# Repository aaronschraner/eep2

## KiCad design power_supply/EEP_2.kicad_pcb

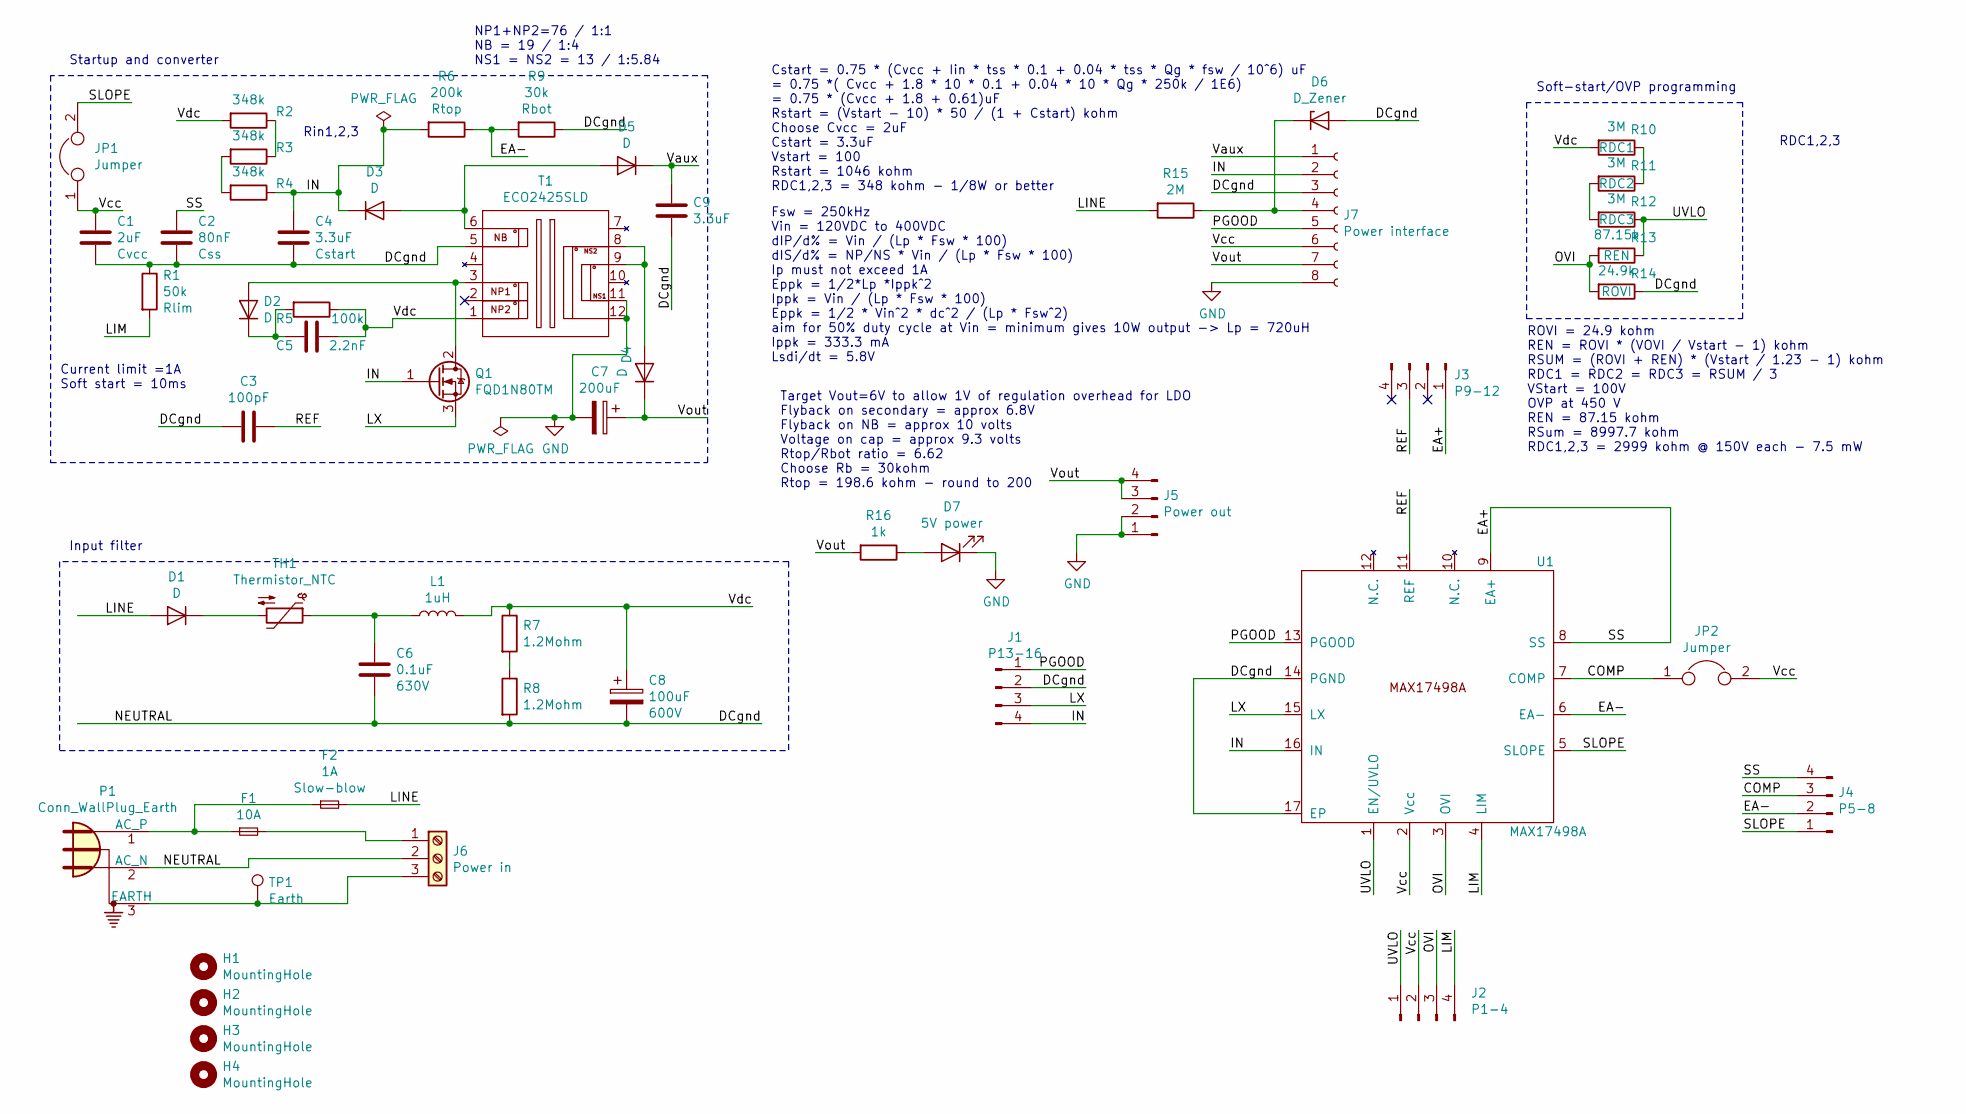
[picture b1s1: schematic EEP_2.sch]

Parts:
C1: 2uF; C_0805_2012Metric
C2: 80nF; C_0805_2012Metric
C3: 100pF; C_0805_2012Metric
C4: 3.3uF; C_1210_3225Metric
C5: 2.2nF; C_0805_2012Metric
C6: 0.1uF; C_2220_5650Metric; Voltage rating 630V
C7: 200uF; CP_Elec_6.3x7.7
C8: 100uF; CP_Radial_D30.0mm_P10.00mm_SnapIn; Voltage rating 600V
C9: 3.3uF; C_0805_2012Metric
D1, D4: D; D_SMC
D2, D3, D5: D; D_SMA
D6: D_Zener; D_SMA
D7: 5V power; LED_0805_2012Metric
F1: 10A; Fuseholder_Cylinder-5x20mm_Schurter_0031_8201_Horizontal_Op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
F2: 1A; Fuseholder_Cylinder-5x20mm_Schurter_0031_8201_Horizontal_Op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
H1, H2, H3, H4: MountingHole; MountingHole_3.2mm_M3_ISO7380
J1: P13-16; PinHeader_1x04_P2.54mm_Vertical
J2: P1-4; PinHeader_1x04_P2.54mm_Vertical
J3: P9-12; PinHeader_1x04_P2.54mm_Vertical
J4: P5-8; PinHeader_1x04_P2.54mm_Vertical
J5: Power out; PinHeader_1x04_P2.54mm_Vertical
J6: Power in; PhoenixContact_GMSTB_2,5_3-GF-7,62_1x03_P7.62mm_Horizontal_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
J7: Power interface; PinSocket_1x08_P2.54mm_Vertical
JP1, JP2: Jumper; SolderJumper-2_P1.3mm_Open_RoundedPad1.0x1.5mm
L1: 1uH; L_1008_2520Metric
P1: Conn_WallPlug_Earth; PhoenixContact_GMSTB_2,5_3-GF-7,62_1x03_P7.62mm_Horizontal_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
Q1: FQD1N80TM; TO-252-2
R1: 50k; R_0805_2012Metric
R2, R3, R4: 348k; R_0805_2012Metric
R5: 100k; R_2512_6332Metric
R6: 200k; R_0805_2012Metric
R7, R8: 1.2Mohm; R_0805_2012Metric
R9: 30k; R_0805_2012Metric
R10, R11, R12: 3M; R_0805_2012Metric
R13: 87.15k; R_0805_2012Metric
R14: 24.9k; R_0805_2012Metric
R15: 2M; R_0805_2012Metric
R16: 1k; R_0805_2012Metric
T1: ECO2425SLD; ECO2425SLD-D01H017
TH1: Thermistor_NTC; R_Axial_DIN0204_L3.6mm_D1.6mm_P5.08mm_Horizontal
TP1: Earth; TestPoint_Loop_D2.50mm_Drill1.0mm
U1: MAX17498A; TQFN-16-1EP_3x3mm_P0.5mm_EP1.23x1.23mm

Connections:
/COMP: J4.3, JP2.1, U1.7 (COMP)
/DCgnd: C1.2, C2.2, C3.2, C4.1, C6.2, C8.2, C9.2, D6.2 (A), J1.2, J6.2, J7.3, P1.2 (AC_N), R1.1, R8.2, R9.1, R14.1, T1.5, U1.14 (PGND), U1.17 (EP)
/EA+: C2.1, J3.1, J4.4, U1.8 (SS), U1.9 (EA+)
/EA-: J4.2, R6.1, R9.2, U1.6 (EA-)
/IN: C4.2, D3.1 (K), J1.4, J7.2, Q1.1 (G), R4.1, R6.2, U1.16 (IN)
/LIM: J2.4, R1.2, U1.4 (LIM)
/LINE: D1.2 (A), F2.2, R15.2
/LX: J1.3, Q1.3 (S), U1.15 (LX)
/OVI: J2.3, R13.2, R14.2, U1.3 (OVI)
/PGOOD: J1.1, J7.5, U1.13 (PGOOD)
/REF: C3.1, J3.3, U1.11 (REF)
/SLOPE: J4.1, JP1.2, U1.5 (SLOPE)
/UVLO: J2.1, R12.1, R13.1, U1.1 (EN/UVLO)
/Vaux: C9.1, D5.1 (K), J7.1
/Vcc: C1.1, J2.2, J7.6, JP1.1, JP2.2, U1.2 (Vcc)
/Vdc: C5.2, C8.1, L1.2, R2.2, R5.1, R7.1, R10.2, T1.1
/Vout: C7.1, D4.1 (K), J5.3, J5.4, J7.7, R16.2
GND: C7.2, D7.1 (K), J5.1, J5.2, J7.8, T1.11, T1.12
unnamed: C5.1, D2.1 (K), R5.2
unnamed: C6.1, L1.1, TH1.1
unnamed: D1.1 (K), TH1.2
unnamed: D2.2 (A), Q1.2 (D), T1.3
unnamed: D3.2 (A), D5.2 (A), T1.6
unnamed: D4.2 (A), T1.8, T1.9
unnamed: D6.1 (K), J7.4, R15.1
unnamed: D7.2 (A), R16.1
unnamed: F1.1, F2.1, P1.1 (AC_P)
unnamed: F1.2, J6.1
unnamed: J6.3, P1.3 (EARTH), TP1.1
unnamed: R2.1, R3.1
unnamed: R3.2, R4.2
unnamed: R7.2, R8.1
unnamed: R10.1, R11.1
unnamed: R11.2, R12.2

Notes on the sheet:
Soft-start/OVP programming
ROVI = 24.9 kohm REN = ROVI * (VOVI / Vstart - 1) kohm RSUM = (ROVI + REN) * (Vstart / 1.23 - 1) kohm RDC1 = RDC2 = RDC3 = RSUM / 3 VStart = 100V OVP at 450 V REN = 87.15 kohm RSum = 8997.7 kohm RDC1,2,3 = 2999 kohm @ 150V each - 7.5 mW
Startup and converter
Input filter
Current limit =1A Soft start = 10ms
Cstart = 0.75 * (Cvcc + Iin * tss * 0.1 + 0.04 * tss * Qg * fsw / 10^6) uF = 0.75 *( Cvcc + 1.8 * 10 * 0.1 + 0.04 * 10 * Qg * 250k / 1E6) = 0.75 * (Cvcc + 1.8 + 0.61)uF Rstart = (Vstart - 10) * 50 / (1 + Cstart) kohm Choose Cvcc = 2uF Cstart = 3.3uF Vstart = 100 Rstart = 1046 kohm RDC1,2,3 = 348 ko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
Rin1,2,3
RDC1,2,3
Fsw = 250kHz Vin = 120VDC to 400VDC dIP/d% = Vin / (Lp * Fsw * 100) dIS/d% = NP/NS * Vin / (Lp * Fsw * 100) Ip must not exceed 1A Eppk = 1/2*Lp *Ippk^2 Ippk = Vin / (Lp * Fsw * 100) Eppk = 1/2 * Vin^2 * dc^2 / (Lp * Fsw^2) aim for 50% duty cycle at Vin = minimum gives 10W output -> Lp = 720uH Ippk 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
NP1+NP2=76 / 1:1 NB = 19 / 1:4 NS1 = NS2 = 13 / 1:5.84
Target Vout=6V to allow 1V of regulation overhead for LDO Flyback on secondary = approx 6.8V Flyback on NB = approx 10 volts Voltage on cap = approx 9.3 volts Rtop/Rbot ratio = 6.62 Choose Rb = 30kohm Rtop = 198.6 kohm - round to 200

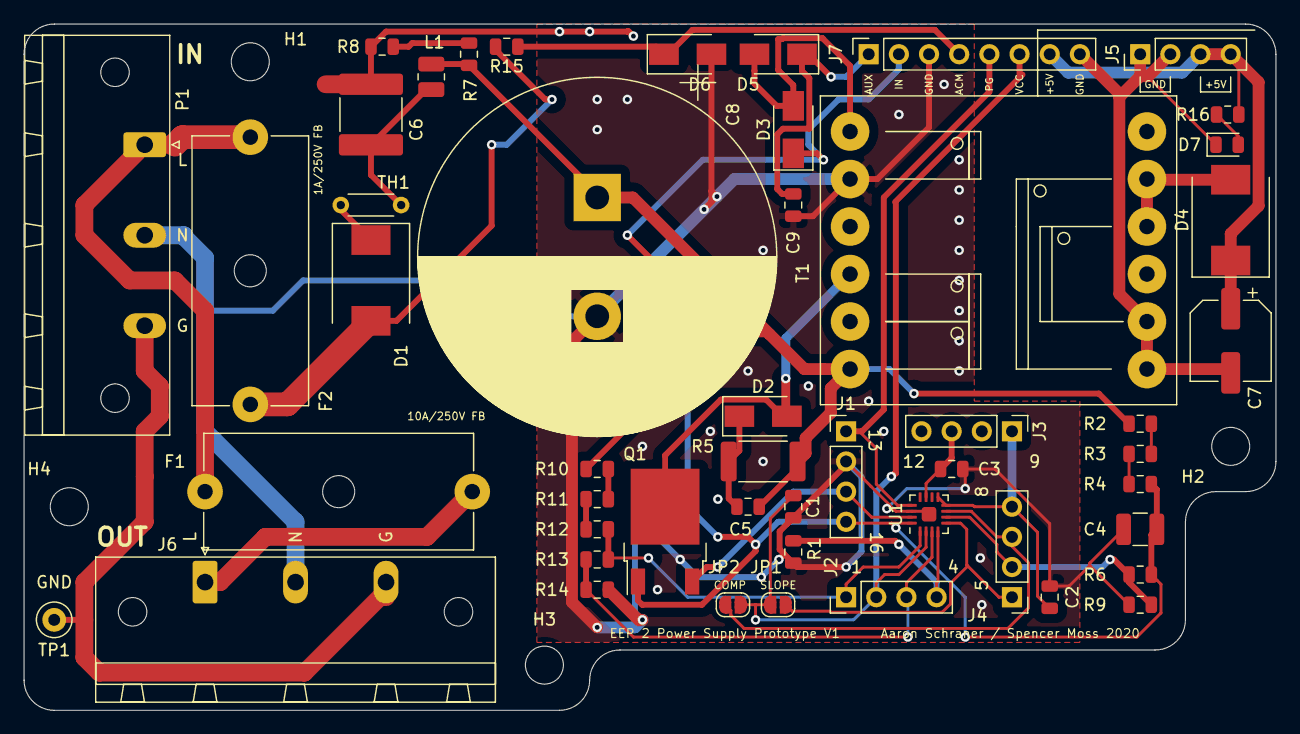
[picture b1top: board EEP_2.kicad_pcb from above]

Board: 2 copper layers, 105.4 x 57.8 mm, 54 parts (0 on the bottom side), 34 nets.

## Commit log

2020-04-04 Created separate directory for power supply
2020-04-04 removed some extraneous files
2020-04-07 Removing binary files, adding gitignore
